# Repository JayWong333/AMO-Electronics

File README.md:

# AMO-Electronics
Collection of electronics projects intended for conducting atomic physics experiments.

## ECDL_CUR_CTRL
This folder contains the schematics and board layout for an ultra-low noise laser diode current controller. It builds upon proven designs of Libbrecht & Hall (https://doi.org/10.1063/1.1143949) as well as Erickson et. al. (https://doi.org/10.1063/1.2953597).

## Analog Temp Controller
This folder contains the schematics and board layout for a thermoelectric cooler controller. It features a PID-loop that drives a Peltier element (or alternatively a resistive heater) in order to match the resistance of a NTC thermistor to a given set temperature.

## Pfeiffer Compact Gauge Controller
A small standalone board which can be used to interface the Pfeiffer PKR/IKR series compact vacuum gauges. Features an ATMEGA32U4 microcontroller to convert the measurement signal to a pressure and provide it via the built-in USB interface or a I2C/SPI display. The accompanying firmware (in form of an Arduino sketch) can be found in the FW folder.

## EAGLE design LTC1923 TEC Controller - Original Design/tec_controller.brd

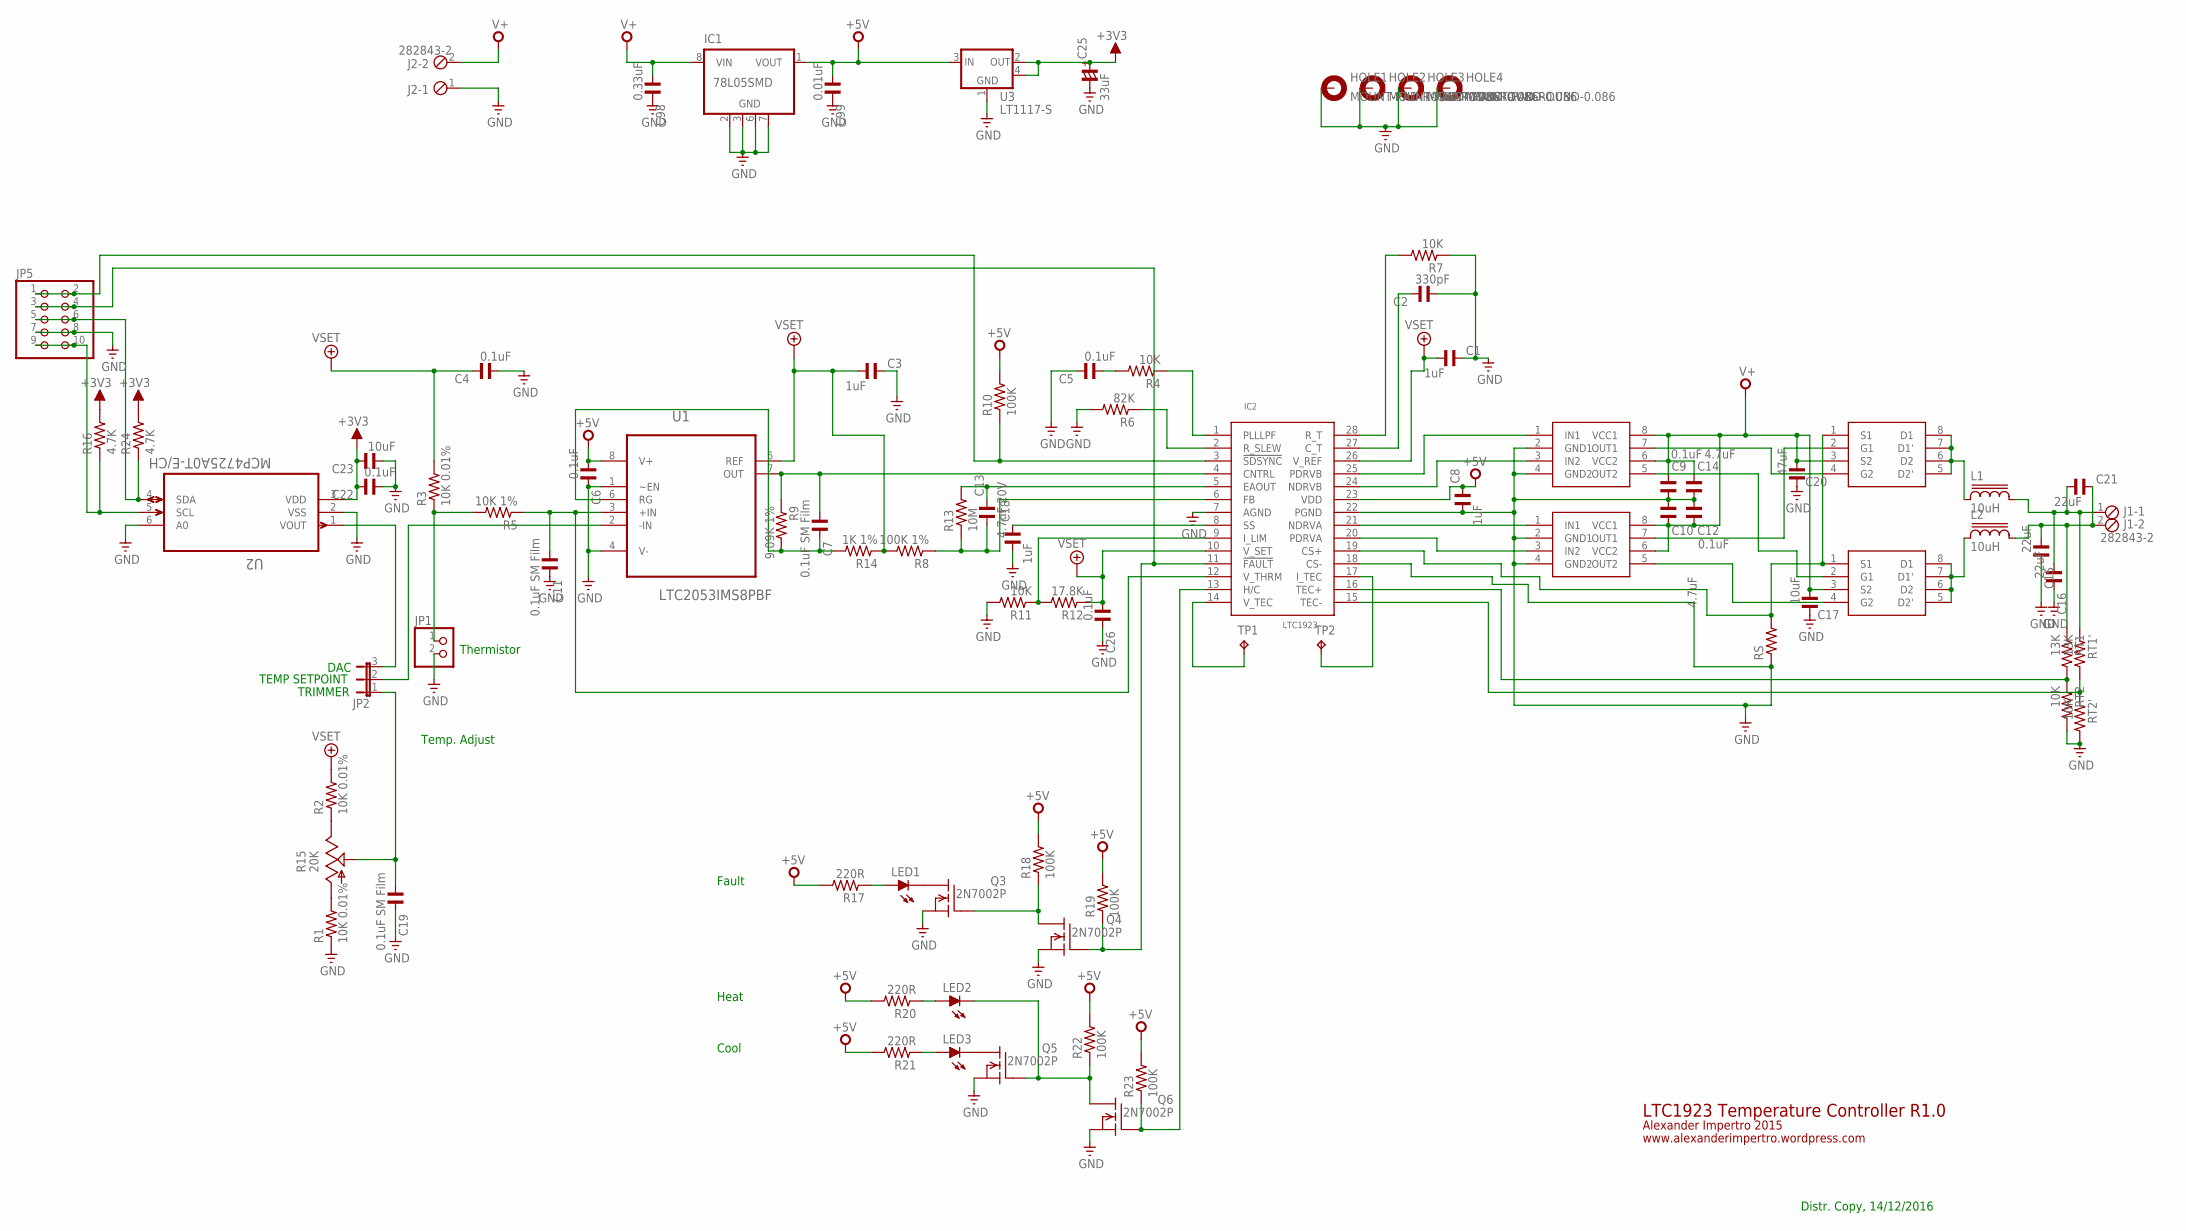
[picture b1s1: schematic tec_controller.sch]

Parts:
C1, C3, C8, C18: 1uF; C0603
C2: 330pF; C0603
C4, C5, C6, C9, C12, C22, C26: 0.1uF; C0603
C7, C11, C19: 0.1uF SM Film; C0805
C10, C14: 4.7uF; C0603
C13: 4.7uF 20V; C1206
C15, C16, C21: 22uF; C0603
C17, C23: 10uF; C0603
C20: 47uF; C0805
C25: 33uF; 153CLV-0505
C98: 0.33uF; C0805
C99: 0.01uF; C0805
HOLE1, HOLE2, HOLE3, HOLE4: MOUNT-PAD-ROUND-0.086; 086-PAD
IC1: 78L05SMD; SO08
IC2: LTC1923; SSOP28
IC3, IC4: LTC1693-1; SO-08
IC5, IC6: IRF7343; SO-08
J1, J2: 282843-2
JP1: PINHD-1X2; 1X02
JP2: JP2E; JP2
JP5: PINHD-2X5; 2X05
L1, L2: 10uH; DRA127
LED1, LED2, LED3: LEDCHIPLED_0805; CHIPLED_0805
Q3, Q4, Q5, Q6: 2N7002P; SOT95P230X110-3N
R1, R2, R3: 10K 0.01%; R0603
R4, R7, R11: 10K; R0603
R5: 10K 1%; R0603
R6: 82K; R0603
R8: 100K 1%; R0603
R9: 9.09K 1%; R0603
R10: 100K; R0805
R12: 17.8K; R0805
R13: 10M; R0805
R14: 1K 1%; R0603
R15: 20K; B25P
R16, R24: 4.7K; R0603
R17, R20, R21: 220R; R0603
R18, R19, R22, R23: 100K; R0603
RS: R-EU_R2512; R2512
RT1, RT1': 13K; R0603
RT2, RT2': 10K; R0603
TP1, TP2: TPTP10SQ; TP10SQ
U1: LTC2053IMS8PBF; SOP65P490X110-8N
U2: MCP4725A0T-E/CH; SOT95P270X145-6N
U3: LT1117-S; SOT223

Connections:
+3V3: C22.1, C23.1, C25.+, R16.2, R24.2, U2.3 (VDD), U3.2 (OUT), U3.4 (TAB)
+5V: C6.2, C8.1, C99.2, IC1.1 (VOUT), IC2.23 (VDD), R10.2, R17.2, R18.2, R19.2, R20.2, R21.2, R22.2, R23.2, U1.8 (V+), U3.3 (IN)
+5V/2: C1.2, C3.2, C4.1, C26.2, IC2.10 (V_SET), IC2.26 (V_REF), R2.2, R3.2, R8.2, R12.1, R14.1, U1.5 (REF)
GND: C1.1, C2.2, C3.1, C4.2, C5.1, C6.1, C8.2, C9.1, C10.2, C11.1, C12.2, C14.1, C15.1, C16.1, C17.1, C18.2, C19.1, C20.1, C22.2, C23.2, C25.-, C26.1, C98.1, C99.1, HOLE1.B086, HOLE2.B086, HOLE3.B086, HOLE4.B086, IC1.2 (GND), IC1.3 (GND), IC1.6 (GND), IC1.7 (GND), IC2.7 (AGND), IC2.18 (CS-), IC2.22 (PGND), IC3.2 (GND1), IC3.4 (GND2), IC4.2 (GND1), IC4.4 (GND2), J2.1, JP1.2, JP5.7, JP5.8, Q3.2 (S), Q4.2 (S), Q5.2 (S), Q6.2 (S), R1.1, R6.2, R7.1, R11.2, RS.1, RT2.2, RT2'.2, U1.1 (~EN), U1.4 (V-), U2.2 (VSS), U2.6 (A0), U3.1 (GND)
unnamed: LED2.C, Q5.1 (G), Q6.3 (D), R22.1
unnamed: C2.1, IC2.27 (C_T)
unnamed: IC2.14 (V_TEC), TP1.TP
unnamed: IC2.17 (I_TEC), TP2.TP
unnamed: IC2.13 (H/C), Q6.1 (G), R23.1
unnamed: IC2.28 (R_T), R7.2
unnamed: LED3.C, Q5.3 (D)
unnamed: LED2.A, R20.1
unnamed: LED3.A, R21.1
unnamed: IC2.11 (!FAULT), JP5.3, JP5.4, Q4.1 (G), R19.1
unnamed: Q3.1 (G), Q4.3 (D), R18.1
unnamed: LED1.C, Q3.3 (D)
unnamed: LED1.A, R17.1
unnamed: C7.2, IC2.4 (CNTRL), R9.1, U1.7 (OUT)
unnamed: C11.2, IC2.12 (V_THRM), R5.1, U1.3 (+IN)
unnamed: JP1.1, R3.1, R5.2
unnamed: C7.1, R9.2, R14.2, U1.6 (RG)
unnamed: JP2.2, U1.2 (-IN)
unnamed: R1.2, R15.A
unnamed: R2.1, R15.E
unnamed: IC2.9 (I_LIM), R11.1, R12.2
unnamed: IC2.2 (R_SLEW), R6.1
unnamed: JP2.3, U2.1 (VOUT)
unnamed: C18.1, IC2.8 (SS)
unnamed: C5.2, R4.2
unnamed: IC2.1 (PLLLPF), R4.1
unnamed: C13.2, IC2.6 (FB), R8.1, R13.1
unnamed: C13.1, IC2.5 (EAOUT), R13.2
unnamed: C19.2, JP2.1, R15.S
unnamed: IC2.16 (TEC+), RT1.2, RT2.1
unnamed: IC2.25 (PDRVB), IC3.1 (IN1)
unnamed: IC2.24 (NDRVB), IC3.3 (IN2)
unnamed: IC2.21 (NDRVA), IC4.1 (IN1)
unnamed: IC2.20 (PDRVA), IC4.3 (IN2)
unnamed: IC2.15 (TEC-), RT1'.2, RT2'.1
unnamed: IC2.3 (!SDSYNC), JP5.1, JP5.2, R10.1
unnamed: IC2.19 (CS+), IC5.1 (S1), IC6.1 (S1), RS.2
unnamed: IC4.7 (OUT1), IC5.2 (G1)
unnamed: IC3.7 (OUT1), IC5.4 (G2)
unnamed: IC3.5 (OUT2), IC6.2 (G1)
unnamed: C16.2, C21.2, J1.1, L1.2, RT1'.1
unnamed: C15.2, C21.1, J1.2, L2.2, RT1.1
unnamed: IC5.5 (D2'), IC5.6 (D2), IC5.7 (D1'), IC5.8 (D1), L1.1
unnamed: IC6.5 (D2'), IC6.6 (D2), IC6.7 (D1'), IC6.8 (D1), L2.1
unnamed: JP5.5, JP5.6, R24.1, U2.4 (SDA)
unnamed: JP5.9, JP5.10, R16.1, U2.5 (SCL)
unnamed: IC4.5 (OUT2), IC6.4 (G2)
V+: C9.2, C10.1, C12.1, C14.2, C17.2, C20.2, C98.2, IC1.8 (VIN), IC3.6 (VCC2), IC3.8 (VCC1), IC4.6 (VCC2), IC4.8 (VCC1), IC5.3 (S2), IC6.3 (S2), J2.2

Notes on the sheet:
Cool
Heat
Fault
Thermistor
Temp. Adjust
TEMP SETPOINT
DAC
TRIMMER
Alexander Impertro 2015
www.alexanderimpertro.wordpress.com
LTC1923 Temperature Controller R1.0
Distr. Copy, 14/12/2016

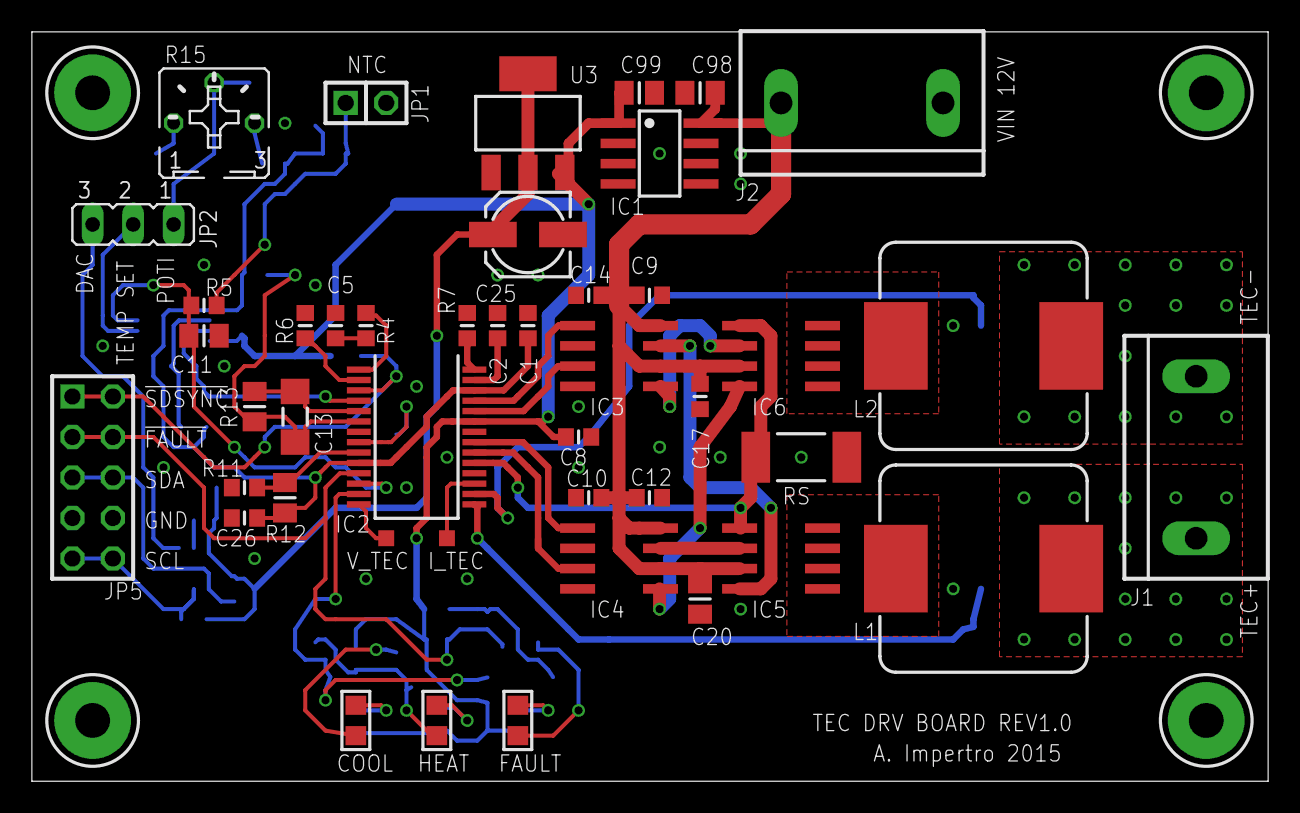
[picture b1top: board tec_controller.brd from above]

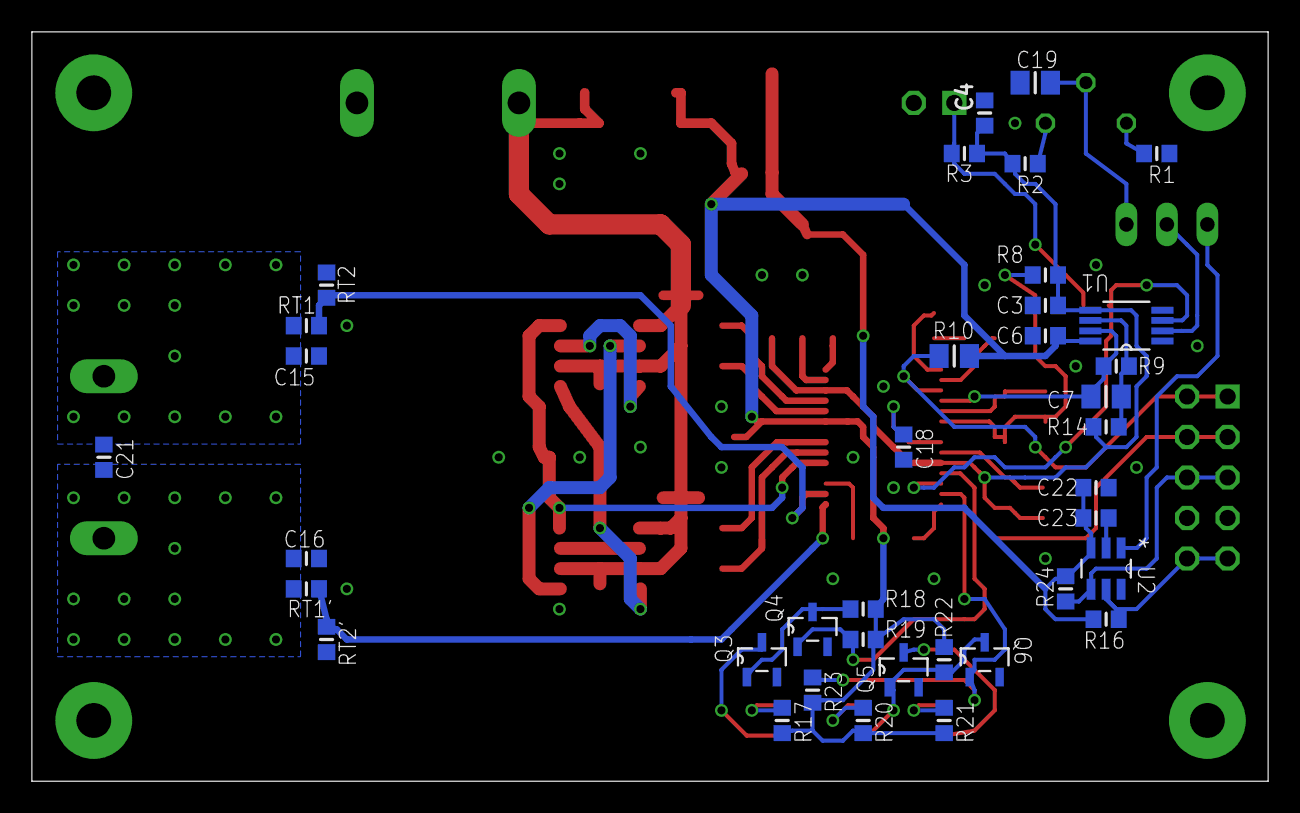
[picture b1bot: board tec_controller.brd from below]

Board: 2 copper layers, 77.5 x 47.0 mm, 85 parts (37 on the bottom side), 52 nets.

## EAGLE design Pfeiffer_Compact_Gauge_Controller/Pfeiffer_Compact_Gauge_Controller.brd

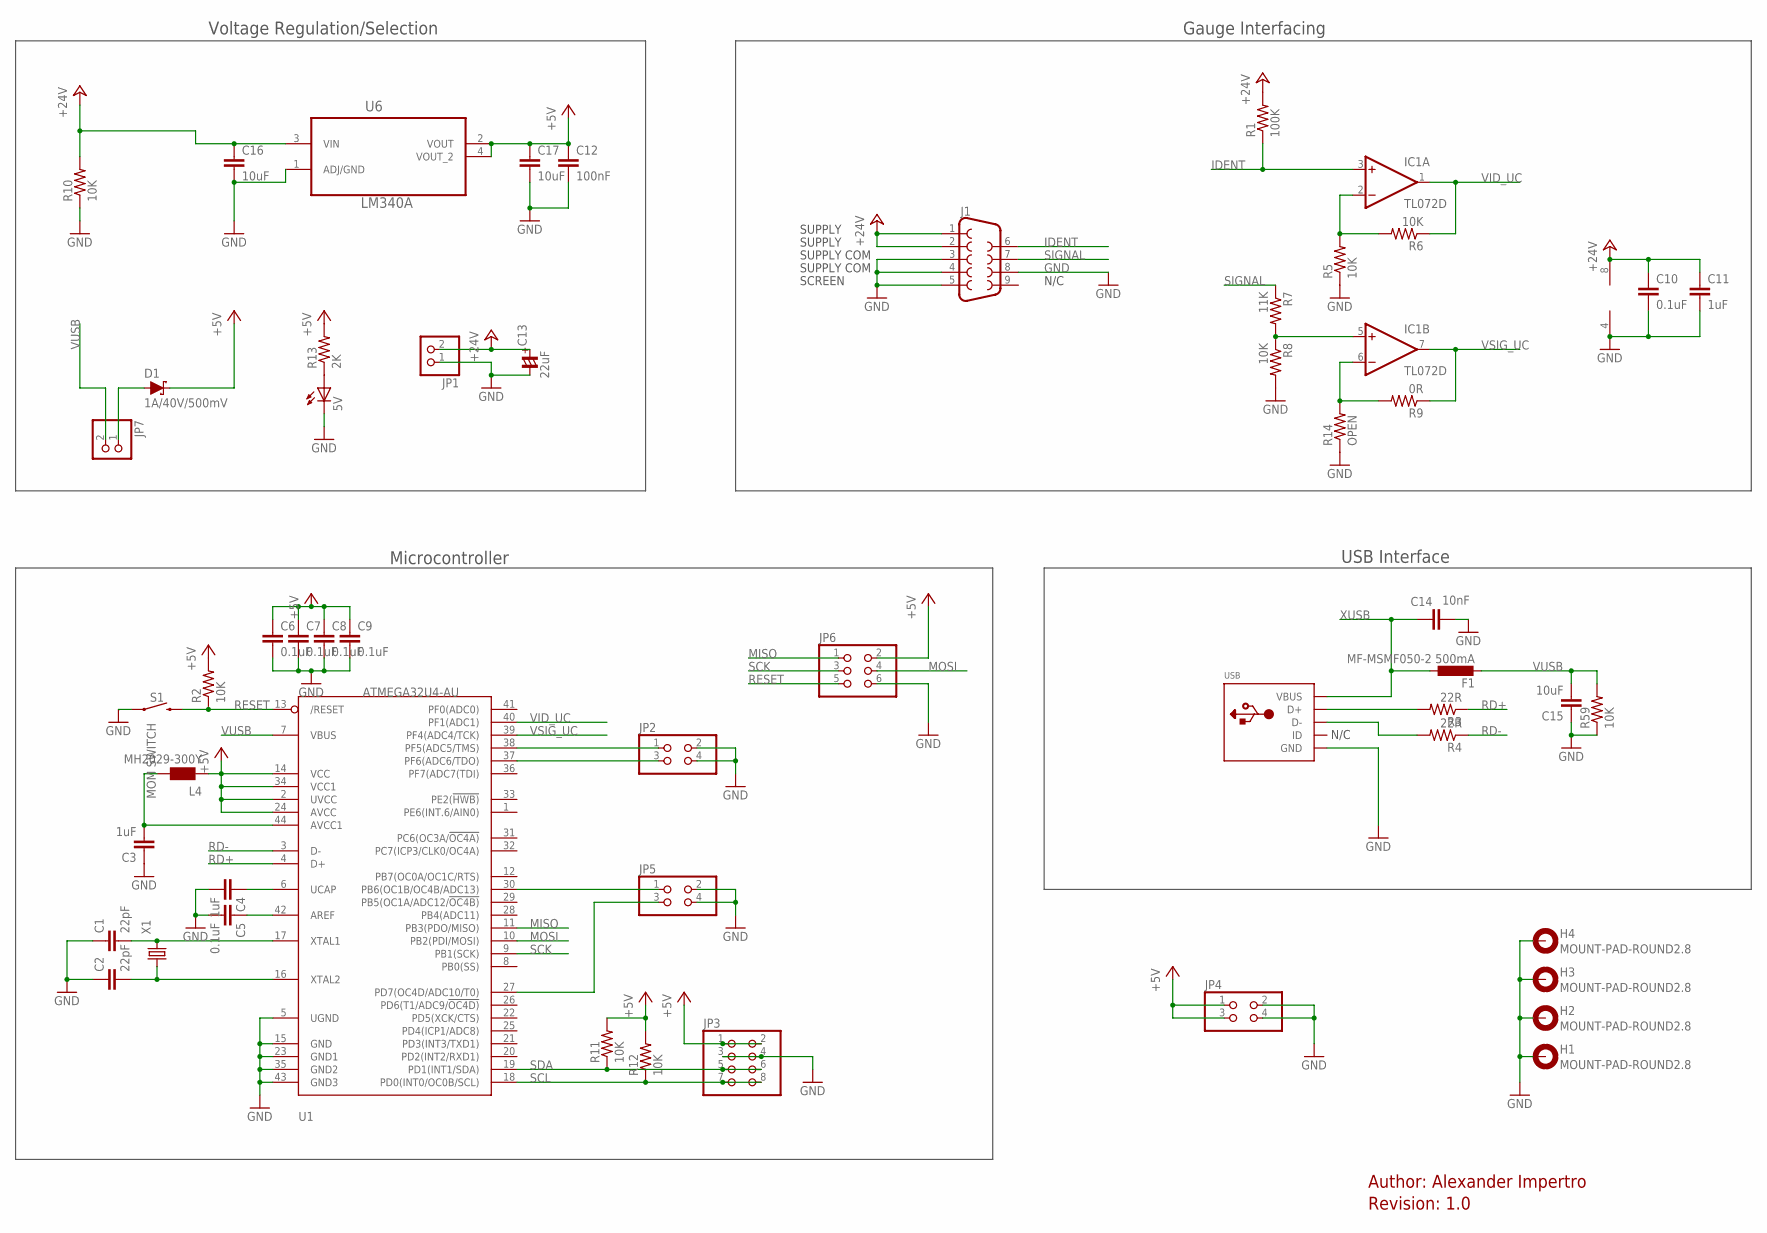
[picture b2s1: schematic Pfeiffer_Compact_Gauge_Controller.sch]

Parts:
5V: LEDCHIPLED_0805; CHIPLED_0805
C1, C2: 22pF; C0805
C3, C4, C11: 1uF; C0805
C5, C6, C7, C8, C9, C10: 0.1uF; C0805
C12: 100nF; C0805
C13: 22uF; CSV-C
C14: 10nF; C0805
C15, C16, C17: 10uF; C0805
D1: 1A/40V/500mV; SMA-DIODE
F1: MF-MSMF050-2 500mA; PROTEZIONE_L1812
H1, H2, H3, H4: MOUNT-PAD-ROUND2.8; 2,8-PAD
IC1: TL072D; SO08
J1: DB9MALE; DB9_MALE
JP1: PINHD-1X2/90; 1X02/90
JP2, JP4, JP5: PINHD-2X2; 2X02
JP3: PINHD-2X4; 2X04
JP6: PINHD-2X3; 2X03
JP7: PINHD-1X2; 1X02
L4: MH2029-300Y; PROTEZIONE_0805
R1: 100K; R0805
R2, R5, R6, R8, R10, R11, R12, R59: 10K; R0805
R3, R4: 22R; R0805
R7: 11K; R0805
R9: 0R; R0805
R13: 2K; R0805
R14: OPEN; R0805
S1: MOM SWITCH; TACTILE_SWITCH_SMD_5.2MM
U1: ATMEGA32U4-AU; TQFP44
U6: LM340A; SOT230P696X180-4N
USB: USBMINIB; USB-MINIB
X1: KX-7; 3.2X2.5_KX-7

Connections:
+5V: C6.1, C7.1, C8.1, C9.1, C12.1, C17.1, D1.C, JP3.1, JP3.2, JP4.1, JP4.3, JP6.2, L4.1, R2.2, R11.2, R12.2, R13.2, U1.2 (UVCC), U1.14 (VCC), U1.24 (AVCC), U1.34 (VCC1), U6.2 (VOUT), U6.4 (VOUT_2)
+24V: C10.1, C11.1, C13.+, C16.1, IC1.8 (V+), J1.1, J1.2, JP1.2, R1.2, R10.2, U6.3 (VIN)
GND: 5V.C, C1.1, C2.1, C3.1, C4.2, C5.2, C6.2, C7.2, C8.2, C9.2, C10.2, C11.2, C12.2, C13.-, C14.2, C15.1, C16.2, C17.2, H1.B2,8, H2.B2,8, H3.B2,8, H4.B2,8, IC1.4 (V-), J1.3, J1.4, J1.5, J1.8, JP1.1, JP2.2, JP2.4, JP3.3, JP3.4, JP4.2, JP4.4, JP5.2, JP5.4, JP6.6, R5.1, R8.2, R10.1, R14.1, R59.1, S1.1, U1.5 (UGND), U1.15 (GND), U1.23 (GND1), U1.35 (GND2), U1.43 (GND3), U6.1 (ADJ/GND), USB.GND
IDENT: IC1.3 (+IN), J1.6, R1.1
MISO: JP6.1, U1.11 (PB3(PDO/MISO))
MOSI: JP6.4, U1.10 (PB2(PDI/MOSI))
unnamed: C1.2, U1.17 (XTAL1), X1.3 (2)
unnamed: C2.2, U1.16 (XTAL2), X1.1
unnamed: C3.2, L4.2, U1.44 (AVCC1)
unnamed: C4.1, U1.6 (UCAP)
unnamed: C5.1, U1.42 (AREF)
unnamed: R3.2, USB.D+
unnamed: R4.2, USB.D-
unnamed: IC1.2 (-IN), R5.2, R6.2
unnamed: IC1.6 (-IN), R9.2, R14.2
unnamed: IC1.5 (+IN), R7.2, R8.1
unnamed: JP2.1, U1.38 (PF5(ADC5/TMS))
unnamed: D1.A, JP7.1
unnamed: JP2.3, U1.37 (PF6(ADC6/TDO))
unnamed: JP5.1, U1.30 (PB6(OC1B/OC4B/ADC13))
unnamed: JP5.3, U1.27 (PD7(OC4D/ADC10/T0))
unnamed: 5V.A, R13.1
RD+: R3.1, U1.4 (D+)
RD-: R4.1, U1.3 (D-)
RESET: JP6.5, R2.1, S1.3 (2), U1.13 (/RESET)
SCK: JP6.3, U1.9 (PB1(SCK))
SCL: JP3.7, JP3.8, R12.1, U1.18 (PD0(INT0/OC0B/SCL))
SDA: JP3.5, JP3.6, R11.1, U1.19 (PD1(INT1/SDA))
SIGNAL: J1.7, R7.1
VID_UC: IC1.1 (OUT), R6.1, U1.40 (PF1(ADC1))
VSIG_UC: IC1.7 (OUT), R9.1, U1.39 (PF4(ADC4/TCK))
VUSB: C15.2, F1.2, JP7.2, R59.2, U1.7 (VBUS)
XUSB: C14.1, F1.1, USB.VBUS

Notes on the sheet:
SUPPLY
SUPPLY COM
SCREEN
N/C
Author: Alexander Impertro
Revision: 1.0
Voltage Regulation/Selection
Microcontroller
Gauge Interfacing
USB Interface

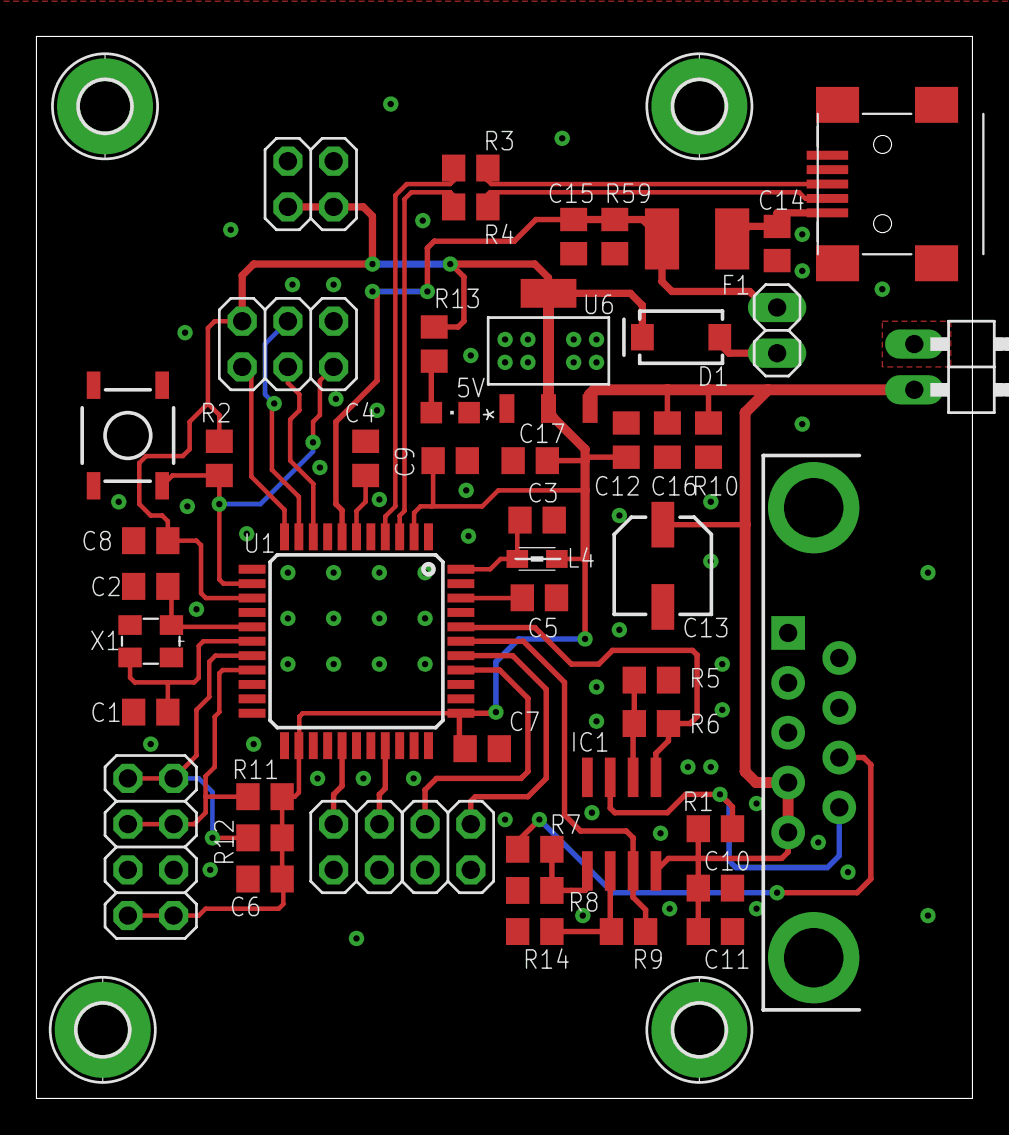
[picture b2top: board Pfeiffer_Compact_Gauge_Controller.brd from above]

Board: 2 copper layers, 52.0 x 59.0 mm, 54 parts (0 on the bottom side), 33 nets.

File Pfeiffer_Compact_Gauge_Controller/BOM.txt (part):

Partlist exported from C:/Users/alexi/OneDrive/MOTATHOME/780nm Laser Source/AMO-Electronics/Pfeiffer_Compact_Gauge_Controller/Pfeiffer_Compact_Gauge_Controller.sch at 1/28/2018 9:25 PM

Qty Value              Device                                       Package                  Parts                              Description                          CASE MONTHLY_USAGE MPN           OC_FARNELL OC_NEWARK PACKAGE PART_NUMBER                  PRICE PROD_ID    SF_SKU    SPICEPREFIX SUPPLIER               TYPE       VALUE             
1                      DB9MALE                                      DB9_MALE                 J1                                 DB9 Connector                                                                                                                         CONN-09904                                                                           
1                      KX-7                                         3.2X2.5_KX-7             X1                                 Quartz Crystals (MHz) SMD:                                                                                                                                                                                                 
1                      LEDCHIPLED_0805                              CHIPLED_0805             5V                                 LED                                                                                                                                                                                                                        
1                      PINHD-1X2                                    1X02                     JP7                                PIN HEADER                                                                                                                                                                                                                 
1                      PINHD-1X2/90                                 1X02/90                  JP1                                PIN HEADER                                                                                                                                                                                                                 
3                      PINHD-2X2                                    2X02                     JP2, JP4, JP5                      PIN HEADER                                                                                                                                                                                                                 
1                      PINHD-2X3                                    2X03                     JP6                                PIN HEADER                                                                                                                                                                                                                 
1                      PINHD-2X4                                    2X04                     JP3                                PIN HEADER                                                                                                                                                                                                                 
1                      USBMINIB                                     USB-MINIB                USB                                USB Connectors                                                                                                                                                                                                             
6   0.1uF              C-EUC0805                                    C0805                    C5, C6, C7, C8, C9, C10            CAPACITOR, European symbol                                                                                                                                 C                                                               
1   0R                 R-US_R0805                                   R0805                    R9                                 RESISTOR, American symbol                                                                                                                                  R                                                               
1   100K               R-US_R0805                                   R0805                    R1                                 RESISTOR, American symbol                                                                                                                                  R                                                               
1   100nF              C-EUC0805                                    C0805                    C12                                CAPACITOR, European symbol                                                                                                                                 C                                                               
8   10K                R-US_R0805                                   R0805                    R2, R5, R6, R8, R10, R11, R12, R59 RESISTOR, American symbol                                                                                                                                  R                                                               
1   10nF               C-EUC0805                                    C0805                    C14                                CAPACITOR, European symbol                                                                                                                                 C                                                               
3   10uF               C-EUC0805                                    C0805                    C15, C16, C17                      CAPACITOR, European symbol                                                                                                                                 C                                                               
1   11K                R-US_R0805                                   R0805                    R7                                 RESISTOR, American symbol                                                                                                                                  R                                                               
1   1A/40V/500mV       DIODE-SCHOTTKY-SS14                          SMA-DIODE                D1                                 Schottky diode                                                                                                                        DIO-08053                                                          1A/40V/500mV      
3   1uF                C-EUC0805                                    C0805                    C3, C4, C11                        CAPACITOR, European symbol                                                                                                                                 C                                                               
2   22R                R-US_R0805                                   R0805                    R3, R4                             RESISTOR, American symbol                                                                                                                                  R                                                               
2   22pF               C-EUC0805                                    C0805                    C1, C2                             CAPACITOR, European symbol                                                                                                                                 C                                                               
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
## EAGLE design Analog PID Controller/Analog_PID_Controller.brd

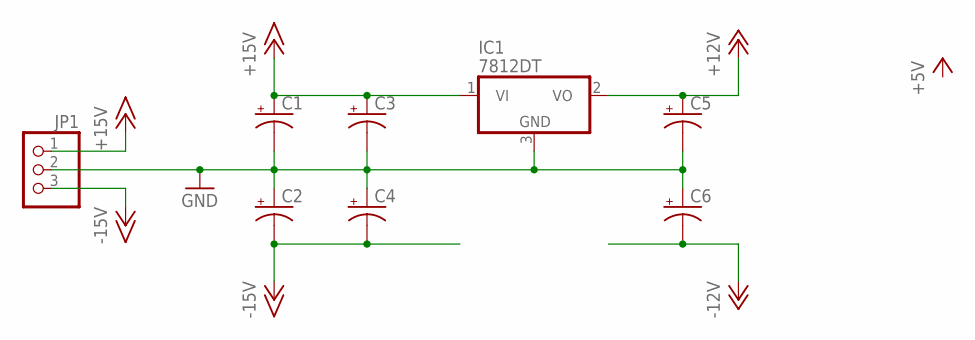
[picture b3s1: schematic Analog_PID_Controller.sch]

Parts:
C1, C2, C3, C4, C5, C6: CPOL-USD; PANASONIC_D
IC1: 7812DT; TO252
JP1: PINHD-1X3/90; 1X03/90

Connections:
+12V: C5.+, IC1.2 (VO)
+15V: C1.+, C3.+, IC1.1 (VI), JP1.1
-12V: C6.-
-15V: C2.-, C4.-, JP1.3
GND: C1.-, C2.+, C3.-, C4.+, C5.-, C6.+, IC1.3 (GND), JP1.2

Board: 2 copper layers, 8 parts (0 on the bottom side), 4 nets, no tracks yet.

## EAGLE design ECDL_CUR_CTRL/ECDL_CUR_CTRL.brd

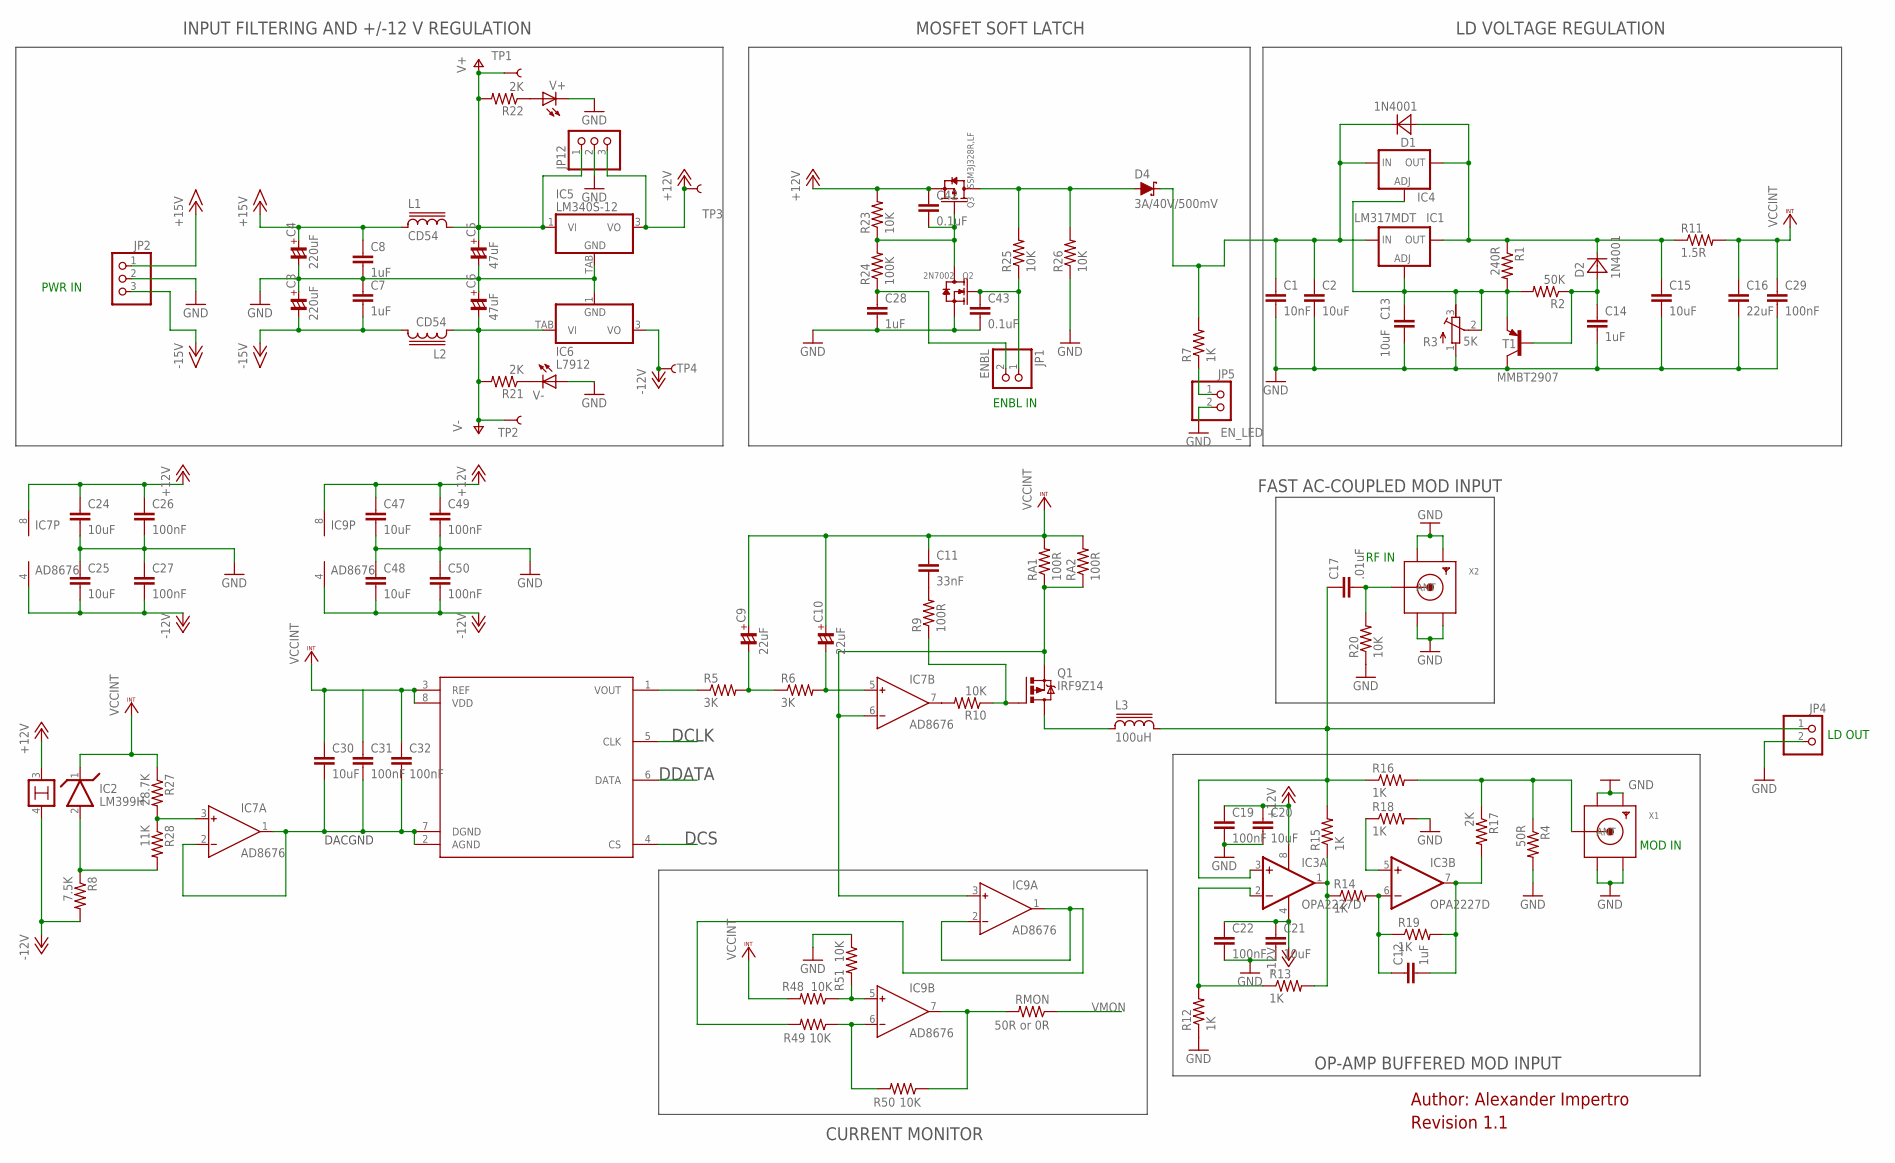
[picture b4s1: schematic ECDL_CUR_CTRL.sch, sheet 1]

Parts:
C1: 10nF; C0805
C2, C13, C15, C20, C21, C24, C25, C30, C47, C48: 10uF; C0805
C3, C4: 220uF; CSV-D
C5, C6: 47uF; C3528-21R/T
C7, C8, C12, C14, C28: 1uF; C0805
C9, C10: 22uF; CSV-C
C11: 33nF; C0805
C16: 22uF; C0805
C17: .01uF; C0805
C19, C22, C26, C27, C29, C31, C32, C49, C50: 100nF; C0805
C42, C43: 0.1uF; C0805
D1, D2: 1N4001; SMA
D4: 3A/40V/500mV; SMA-DIODE
IC1: LM317MDT; DPACK
IC2: LM399H; TO39/4
IC3: OPA2227D; SO08
IC4: LM317TS; 317TS
IC5: LM340S-12; TO263-3
IC6: L7912; TO223-3
IC7, IC9: AD8676; SO8
JP1: ENBL; 1X02
JP2: PINHD-1X3/90; 1X03/90
JP4: PINHD-1X2/90; 1X02/90
JP5: EN_LED; 1X02
JP12: PINHD-1X3; 1X03
L1, L2: CD54
L3: 100uH; CD54
Q1: IRF9Z14; TO220BV
Q2: 2N7002; SOT-23
Q3: SSM3J328R,LF; SOT-23
R1: 240R; R0805
R2: 50K; R0805
R3: 5K; RTRIM3296W
R4: 50R; R0805
R5, R6: 3K; R0805
R7, R12, R13, R14, R15, R16, R18, R19: 1K; R0805
R8: 7.5K; R0805
R9: 100R; R0805
R10, R20, R23, R25, R26, R48, R49, R50, R51: 10K; R0805
R11: 1.5R; R2512
R17, R21, R22: 2K; R0805
R24: 100K; R0805
R27: 28.7K; R0805
R28: 11K; R0805
RA1, RA2: 100R; R2512
RMON: 50R or 0R; R0805
T1: MMBT2907; SOT23-BEC
TP1, TP2, TP3, TP4: TEST-POINT2; PAD.02X.02
U3: AD5541; SOIC-8
V+: LEDCHIPLED_0805; CHIPLED_0805
V-: LEDCHIPLED_0805; CHIPLED_0805
X1, X2: SMACONNECTOR; SMA90_DIP

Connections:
+12V: C19.1, C20.1, C24.1, C26.1, C42.1, C47.1, C49.1, IC2.3, IC3.8 (V+), IC5.3 (VO), IC7.8 (V+), IC9.8 (V+), JP12.3, Q3.2 (S), R23.2, TP3.P$1; also elsewhere on the board
+15V: C4.+, C8.1, JP2.1, L1.1
-12V: C21.1, C22.1, C25.2, C27.2, C48.2, C50.2, IC2.4, IC3.4 (V-), IC6.3 (VO), IC7.4 (V-), IC9.4 (V-), R8.2, TP4.P$1; also elsewhere on the board
-15V: C3.-, C7.2, JP2.3, L2.2
DACGND: C30.2, C31.2, C32.2, IC7.1 (OUT), IC7.2 (IN-), U3.2 (AGND), U3.7 (DGND); also elsewhere on the board
DCLK: U3.5 (CLK); also elsewhere on the board
DCS: U3.4 (CS); also elsewhere on the board
DDATA: U3.6 (DATA); also elsewhere on the board
GND: C1.2, C2.2, C3.+, C4.-, C5.-, C6.+, C7.1, C8.2, C13.2, C14.2, C15.2, C16.2, C19.2, C20.2, C21.2, C22.2, C24.2, C25.1, C26.2, C27.1, C28.2, C29.2, C43.2, C47.2, C48.1, C49.2, C50.1, IC5.TAB (GND), IC6.1 (GND), JP2.2, JP4.2, JP5.2, JP12.2, Q2.2 (S), R3.1 (A), R4.2, R12.1, R18.2, R20.1, R26.1, R51.1, T1.C, V+.C, V-.A, X1.GND1, X1.GND2, X1.GND3, X1.GND4, X2.GND1, X2.GND2, X2.GND3, X2.GND4; also elsewhere on the board
unnamed: C13.1, IC1.1 (ADJ), IC4.1 (ADJ), R1.2, R2.2, R3.2 (S), R3.3 (E), T1.E
unnamed: L3.1, Q1.D
unnamed: C14.1, D2.A, R2.1, T1.B
unnamed: C11.2, R9.2
unnamed: R5.1, U3.1 (VOUT)
unnamed: C9.-, R5.2, R6.1
unnamed: C10.-, IC7.5 (IN+), R6.2
unnamed: IC2.2, R8.1, R28.2
unnamed: IC7.7 (OUT), R10.2
unnamed: Q1.G, R9.1, R10.1
unnamed: C43.1, JP1.1, Q2.1 (G), R25.1
unnamed: IC7.6 (IN-), IC9.3 (IN+), Q1.S, RA1.1, RA2.1
unnamed: C12.1, IC3.6 (-IN), R14.2, R19.1
unnamed: IC3.2 (-IN), R12.2, R13.1
unnamed: IC3.1 (OUT), R13.2, R14.1, R15.1
unnamed: C12.2, IC3.7 (OUT), R17.2, R19.2
unnamed: R4.1, R16.2, R17.1, X1.ANTENNA (ANT)
unnamed: IC3.5 (+IN), R18.1
unnamed: C17.2, R20.2, X2.ANTENNA (ANT)
unnamed: R22.1, V+.A
unnamed: R21.1, V-.C
unnamed: C1.1, C2.1, D1.C, D4.C, IC1.3 (IN), IC4.3 (IN), R7.2
unnamed: C28.1, JP1.2, R24.1
unnamed: C15.1, D1.A, D2.C, IC1.4 (OUT), IC4.2 (OUT), R1.1, R11.1
unnamed: C42.2, Q2.3 (D), Q3.1 (G), R23.1, R24.2
unnamed: IC7.3 (IN+), R27.2, R28.1
unnamed: D4.A, Q3.3 (D), R25.2, R26.2
unnamed: C17.1, IC3.3 (+IN), JP4.1, L3.2, R15.2, R16.1
unnamed: JP5.1, R7.1
unnamed: IC9.1 (OUT), IC9.2 (IN-), R49.2
unnamed: IC9.5 (IN+), R48.1, R51.2
unnamed: IC9.6 (IN-), R49.1, R50.2
unnamed: IC9.7 (OUT), R50.1, RMON.2
V+: C5.+, IC5.1 (VI), JP12.1, L1.2, R22.2, TP1.P$1
V-: C6.-, IC6.TAB (VI), L2.1, R21.2, TP2.P$1
VCCINT: C9.+, C10.+, C11.1, C16.1, C29.1, C30.1, C31.1, C32.1, IC2.1, R11.2, R27.1, R48.2, RA1.2, RA2.2, U3.3 (REF), U3.8 (VDD)
VMON: RMON.1; also elsewhere on the board

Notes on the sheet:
MOD IN
LD OUT
RF IN
ENBL IN
PWR IN
Revision 1.1
Author: Alexander Impertro
INPUT FILTERING AND +/-12 V REGULATION
MOSFET SOFT LATCH
LD VOLTAGE REGULATION
DCS
DDATA
DCLK
DACGND
VMON
OP-AMP BUFFERED MOD INPUT
FAST AC-COUPLED MOD INPUT
CURRENT MONITOR

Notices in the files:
parts and their libraries:
SparkFun-IC-Microcontroller: Licensing: Creative Commons ShareAlike 4.0 International - https://creativecommons.org/licenses/by-sa/4.0
inductor-sumida: Copyright (C) 2008, Bob Starr
rc-master-smd: Copyright (C) 2007-2008, Bob Starr
inductor-cooper: Copyright (C) 2010, Bob Starr
